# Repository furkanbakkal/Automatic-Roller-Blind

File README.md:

# Automatic Roller Blind
Remote control roller blind with Arduino

You can visit for tutorial:https://akademi.robolinkmarket.com/arduino-ile-otomatik-stor-perde/

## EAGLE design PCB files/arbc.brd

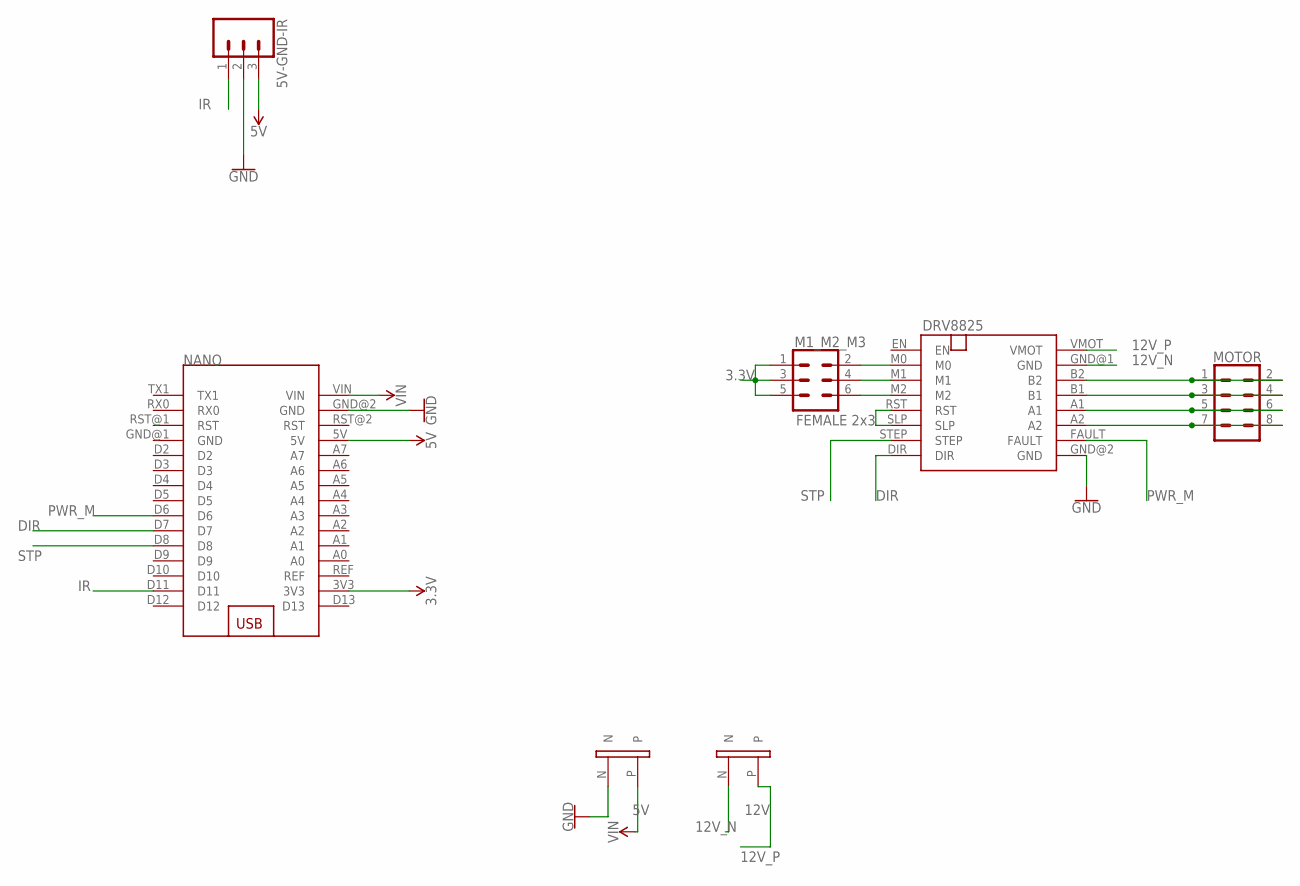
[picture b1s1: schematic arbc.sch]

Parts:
5V, 12V: 5MM_CONNECTOR
5V-GND-IR: CONN_03; 1X03
DRV8825: DRV8825
M1_M2_M3: FEMALE 2x3; 2X3
MOTOR: CONN_04X2; 2X4
NANO: ARDUINO_NANO

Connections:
3.3V: M1_M2_M3.1, M1_M2_M3.3, M1_M2_M3.5, NANO.3V3
5V: 5V-GND-IR.3, NANO.5V
12V_N: 12V.N, DRV8825.GND@1 (GND)
12V_P: 12V.P, DRV8825.VMOT
DIR: DRV8825.DIR, NANO.D7
GND: 5V.N, 5V-GND-IR.2, DRV8825.GND@2 (GND), NANO.GND@2 (GND)
IR: 5V-GND-IR.1, NANO.D11
unnamed: DRV8825.M0, M1_M2_M3.2
unnamed: DRV8825.M1, M1_M2_M3.4
unnamed: DRV8825.M2, M1_M2_M3.6
unnamed: DRV8825.B2, MOTOR.1, MOTOR.2
unnamed: DRV8825.B1, MOTOR.3, MOTOR.4
unnamed: DRV8825.A1, MOTOR.5, MOTOR.6
unnamed: DRV8825.A2, MOTOR.7, MOTOR.8
unnamed: DRV8825.RST, DRV8825.SLP
PWR_M: DRV8825.FAULT, NANO.D6
STP: DRV8825.STEP, NANO.D8
VIN: 5V.P, NANO.VIN

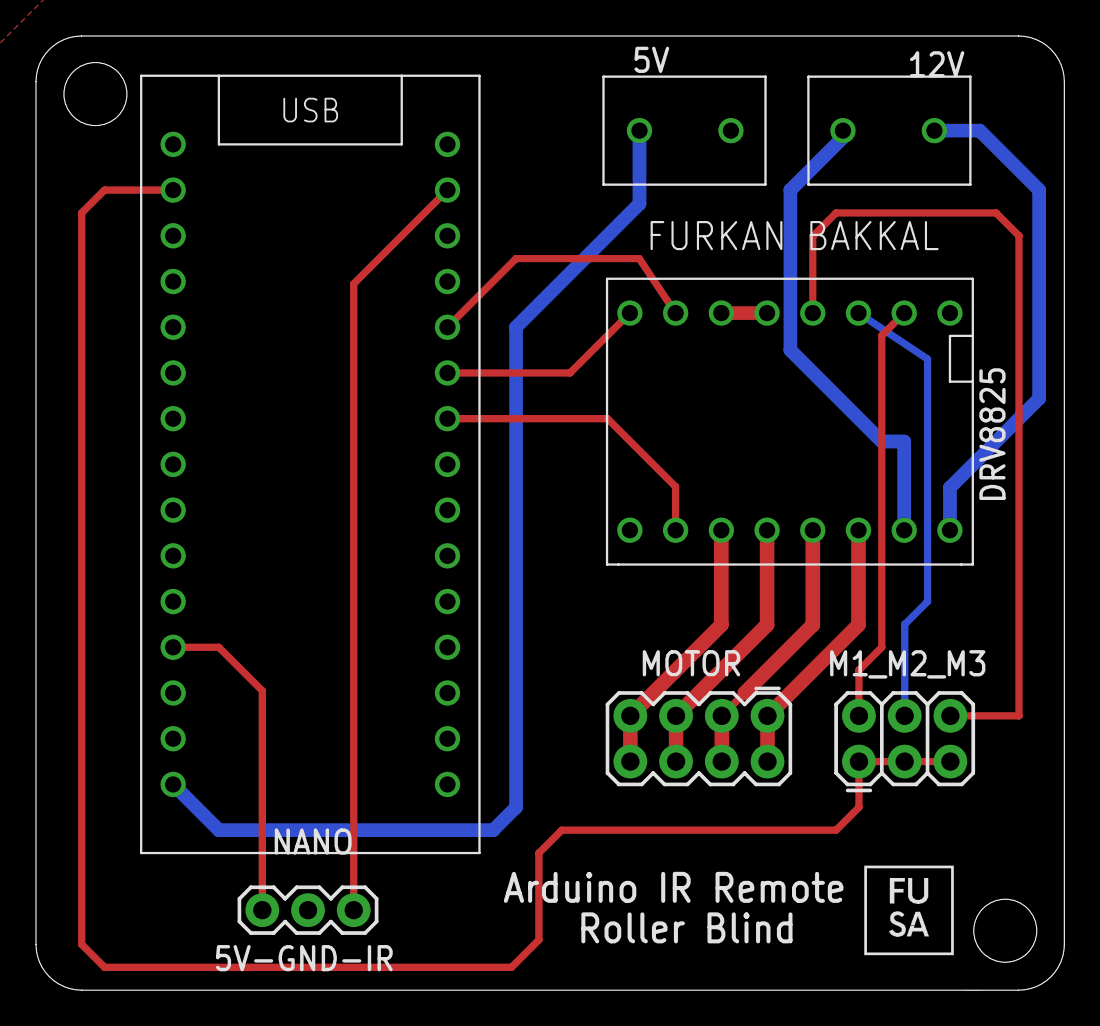
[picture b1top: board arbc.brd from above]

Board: 2 copper layers, 57.1 x 53.0 mm, 7 parts (0 on the bottom side), 18 nets.

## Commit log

2021-03-25 Arduino Code File
2021-03-25 Tutorial File
2021-09-21 STL files added

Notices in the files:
parts and their libraries:
SparkFun-Connectors: Licensing: Creative Commons ShareAlike 4.0 International - https://creativecommons.org/licenses/by-sa/4.0
